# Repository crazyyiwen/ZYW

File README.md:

# ZYW

Dear everyone:

                  This part includes several projects I have done before
                  1 PMSM motor control prototype simulation in Matlab
                  
                  2 CAN PCB design connected to myRIO
                  
                  3 resolver signal processing for PMSM PCB design
                  
                  4 BLDC commercial project PCB design and control(C code)

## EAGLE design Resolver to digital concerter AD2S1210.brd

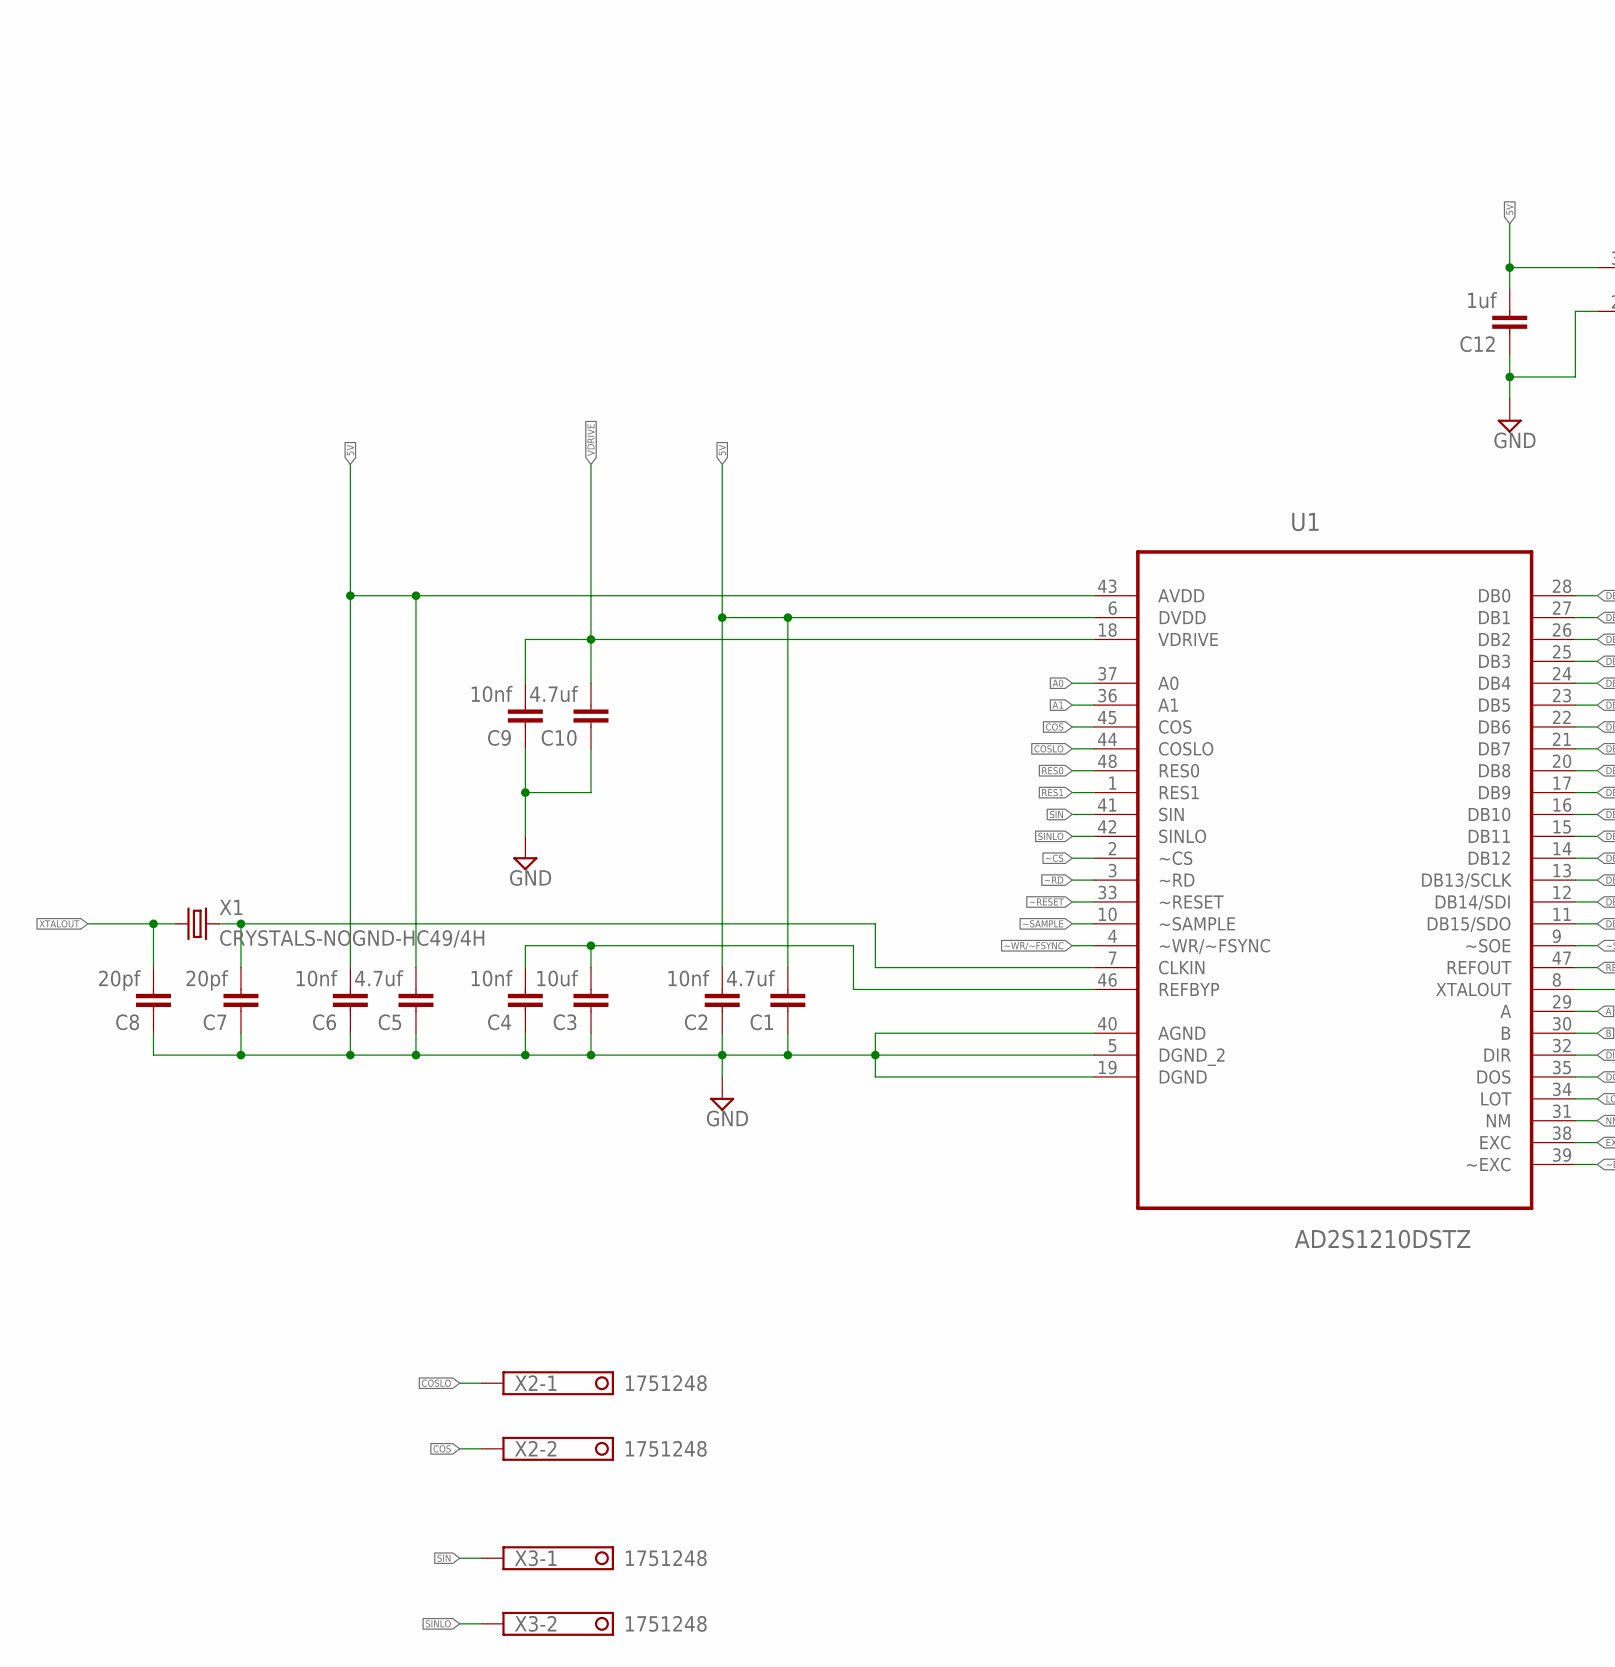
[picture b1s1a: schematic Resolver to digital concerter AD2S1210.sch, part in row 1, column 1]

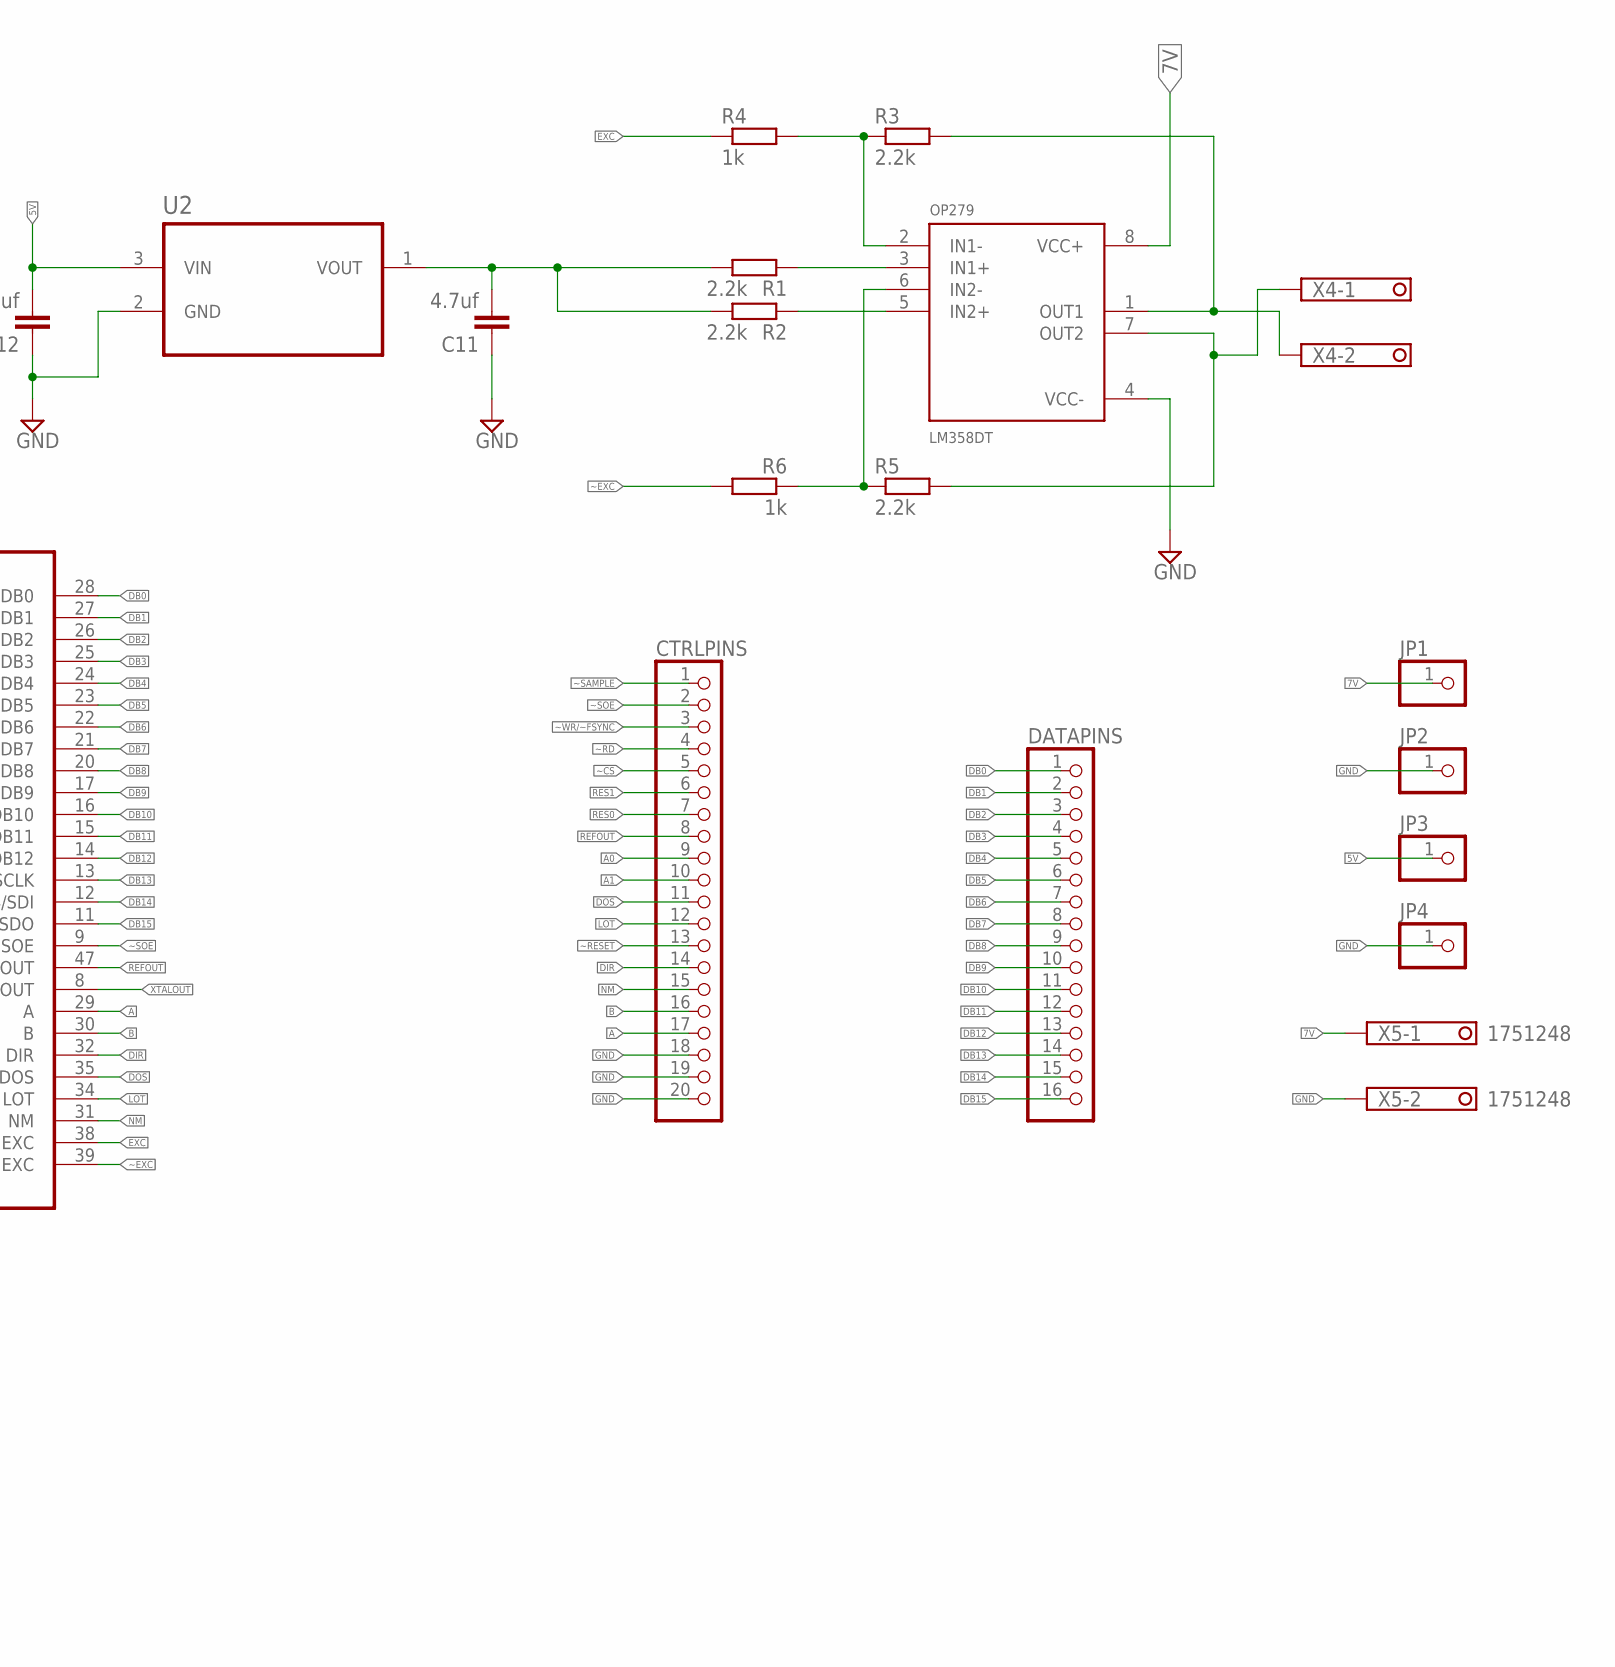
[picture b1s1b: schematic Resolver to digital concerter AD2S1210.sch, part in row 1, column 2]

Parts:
C1, C5, C10, C11: 4.7uf; C0805
C2, C4, C6, C9: 10nf; C0805
C3: 10uf; C0805
C7, C8: 20pf; C0805
C12: 1uf; C0805
CTRLPINS: PINHD-1X20; 1X20
DATAPINS: PINHD-1X16; 1X16
JP1, JP2, JP3, JP4: PINHD-1X1; 1X01
OP279: LM358DT; SOIC127P600X175-8N
R1, R2, R3, R5: 2.2k; R0805
R4, R6: 1k; R0805
U1: AD2S1210DSTZ; QFP50P900X900X160-48N
U2: AD1582BRTZ-REEL7; SOT95P237X112-3N
X1: CRYSTALS-NOGND-HC49/4H; HC49
X2, X3, X4, X5: 1751248

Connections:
5V: C1.2, C2.2, C5.2, C6.2, C12.2, JP3.1, U1.6 (DVDD), U1.43 (AVDD), U2.3 (VIN)
7V: JP1.1, OP279.8 (VCC+), X5.1
A: CTRLPINS.17, U1.29 (A)
A0: CTRLPINS.9, U1.37 (A0)
A1: CTRLPINS.10, U1.36 (A1)
B: CTRLPINS.16, U1.30 (B)
COS: U1.45 (COS), X2.2
COSLO: U1.44 (COSLO), X2.1
DB0: DATAPINS.1, U1.28 (DB0)
DB1: DATAPINS.2, U1.27 (DB1)
DB2: DATAPINS.3, U1.26 (DB2)
DB3: DATAPINS.4, U1.25 (DB3)
DB4: DATAPINS.5, U1.24 (DB4)
DB5: DATAPINS.6, U1.23 (DB5)
DB6: DATAPINS.7, U1.22 (DB6)
DB7: DATAPINS.8, U1.21 (DB7)
DB8: DATAPINS.9, U1.20 (DB8)
DB9: DATAPINS.10, U1.17 (DB9)
DB10: DATAPINS.11, U1.16 (DB10)
DB11: DATAPINS.12, U1.15 (DB11)
DB12: DATAPINS.13, U1.14 (DB12)
DB13: DATAPINS.14, U1.13 (DB13/SCLK)
DB14: DATAPINS.15, U1.12 (DB14/SDI)
DB15: DATAPINS.16, U1.11 (DB15/SDO)
DIR: CTRLPINS.14, U1.32 (DIR)
DOS: CTRLPINS.11, U1.35 (DOS)
EXC: R4.1, U1.38 (EXC)
GND: C1.1, C2.1, C3.1, C4.1, C5.1, C6.1, C7.1, C8.1, C9.1, C10.1, C11.1, C12.1, CTRLPINS.18, CTRLPINS.19, CTRLPINS.20, JP2.1, JP4.1, OP279.4 (VCC-), U1.5 (DGND_2), U1.19 (DGND), U1.40 (AGND), U2.2 (GND), X5.2
LOT: CTRLPINS.12, U1.34 (LOT)
unnamed: OP279.3 (IN1+), R1.1
unnamed: OP279.5 (IN2+), R2.1
unnamed: C11.2, R1.2, R2.2, U2.1 (VOUT)
unnamed: OP279.1 (OUT1), R3.2, X4.2
unnamed: OP279.2 (IN1-), R3.1, R4.2
unnamed: OP279.7 (OUT2), R5.2, X4.1
unnamed: OP279.6 (IN2-), R5.1, R6.1
unnamed: C3.2, C4.2, U1.46 (REFBYP)
unnamed: C7.2, U1.7 (CLKIN), X1.2
NM: CTRLPINS.15, U1.31 (NM)
REFOUT: CTRLPINS.8, U1.47 (REFOUT)
RES0: CTRLPINS.7, U1.48 (RES0)
RES1: CTRLPINS.6, U1.1 (RES1)
SIN: U1.41 (SIN), X3.1
SINLO: U1.42 (SINLO), X3.2
VDRIVE: C9.2, C10.2, U1.18 (VDRIVE)
XTALOUT: C8.2, U1.8 (XTALOUT), X1.1
~CS: CTRLPINS.5, U1.2 (~CS)
~EXC: R6.2, U1.39 (~EXC)
~RD: CTRLPINS.4, U1.3 (~RD)
~RESET: CTRLPINS.13, U1.33 (~RESET)
~SAMPLE: CTRLPINS.1, U1.10 (~SAMPLE)
~SOE: CTRLPINS.2, U1.9 (~SOE)
~WR/~FSYNC: CTRLPINS.3, U1.4 (~WR/~FSYNC)

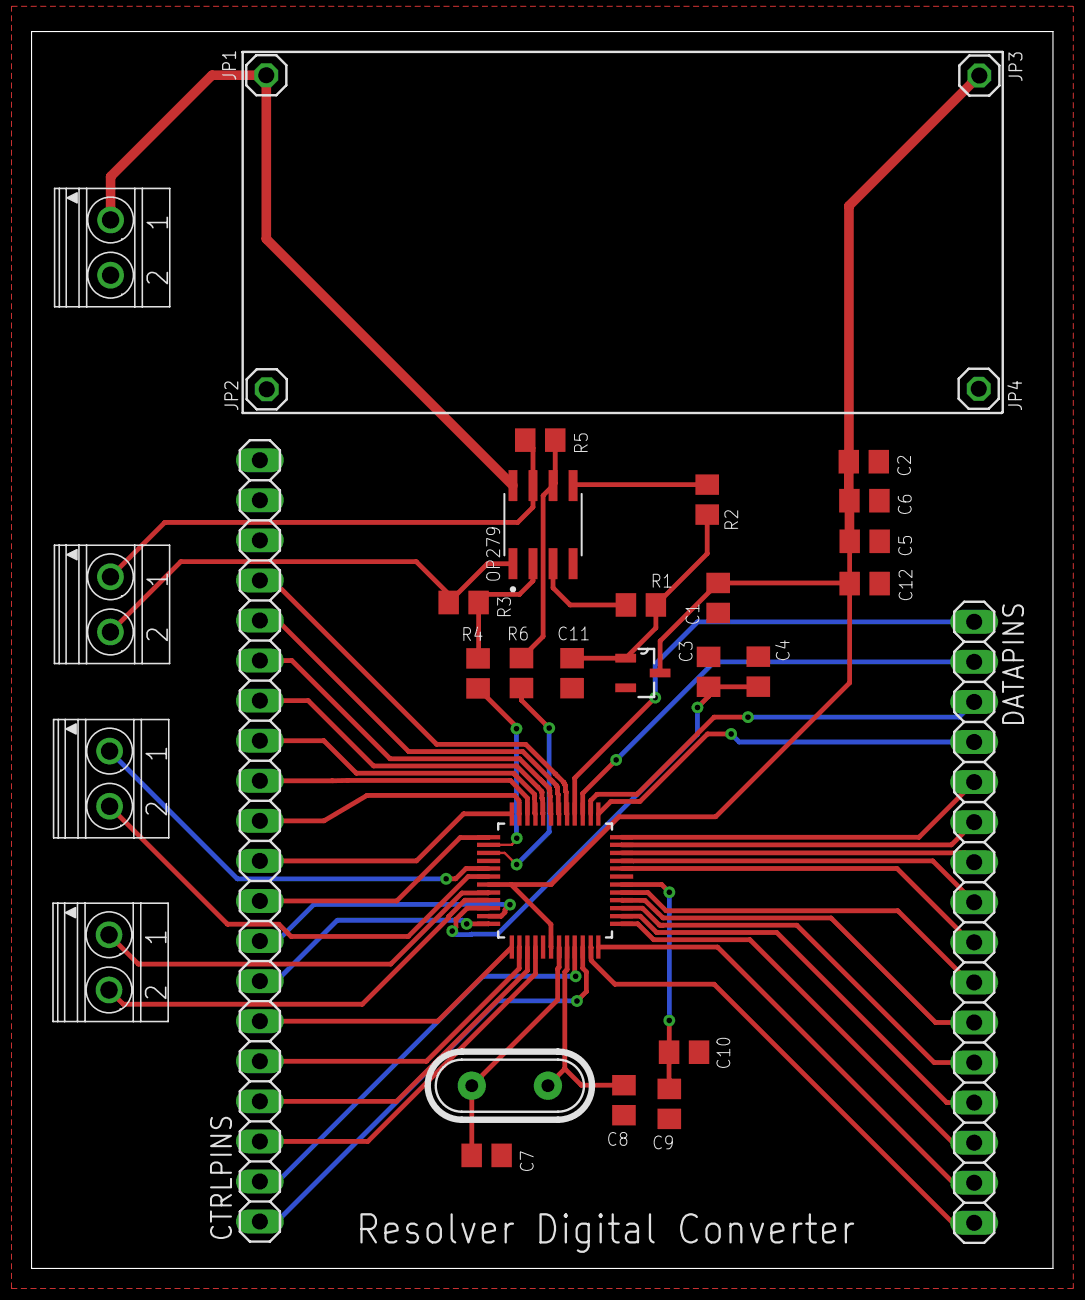
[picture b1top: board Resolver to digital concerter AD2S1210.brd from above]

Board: 2 copper layers, 64.8 x 78.4 mm, 32 parts (0 on the bottom side), 53 nets.

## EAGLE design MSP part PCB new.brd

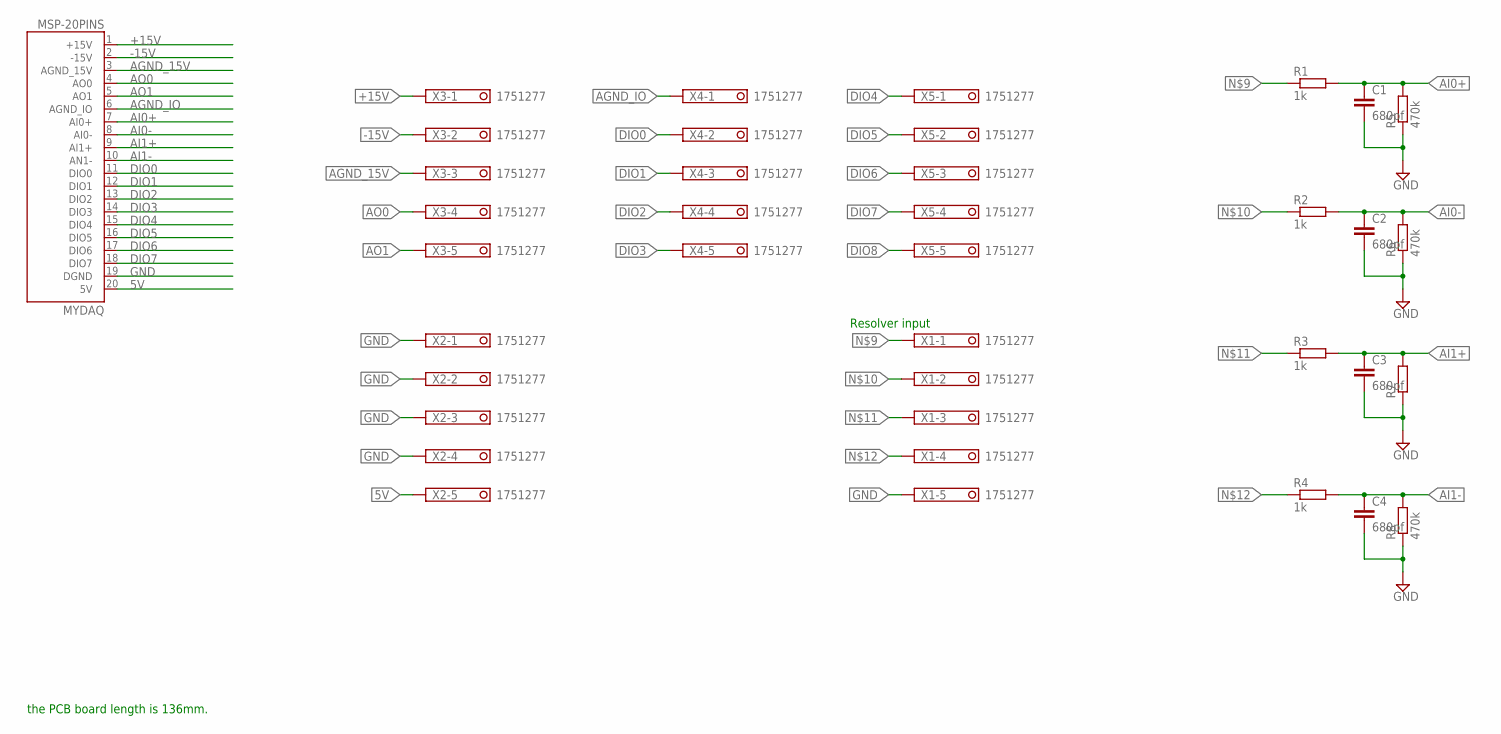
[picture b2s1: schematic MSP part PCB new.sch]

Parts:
C1, C2, C3, C4: 680pf; C050-024X044
MSP-20PINS: MYDAQ; 3.81MM_TERMINAL_BLOCK_FEMALE_LOCKING
R1, R2, R3, R4: 1k; 0204/7
R5, R6, R8: 470k; 0204/7
R7: R-EU_0204/7; 0204/7
X1, X2, X3, X4, X5: 1751277

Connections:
5V: MSP-20PINS.20 (5V), X2.5
+15V: MSP-20PINS.1 (+15V), X3.1
-15V: MSP-20PINS.2 (-15V), X3.2
AGND_15V: MSP-20PINS.3 (AGND_15V), X3.3
AGND_IO: MSP-20PINS.6 (AGND_IO), X4.1
AI0+: C1.1, MSP-20PINS.7 (AI0+), R1.2, R5.2
AI0-: C2.1, MSP-20PINS.8 (AI0-), R2.2, R6.2
AI1+: C3.1, MSP-20PINS.9 (AI1+), R3.2, R7.2
AI1-: C4.1, MSP-20PINS.10 (AN1-), R4.2, R8.2
AO0: MSP-20PINS.4 (AO0), X3.4
AO1: MSP-20PINS.5 (AO1), X3.5
DIO0: MSP-20PINS.11 (DIO0), X4.2
DIO1: MSP-20PINS.12 (DIO1), X4.3
DIO2: MSP-20PINS.13 (DIO2), X4.4
DIO3: MSP-20PINS.14 (DIO3), X4.5
DIO4: MSP-20PINS.15 (DIO4), X5.1
DIO5: MSP-20PINS.16 (DIO5), X5.2
DIO6: MSP-20PINS.17 (DIO6), X5.3
DIO7: MSP-20PINS.18 (DIO7), X5.4
DIO8: X5.5
GND: C1.2, C2.2, C3.2, C4.2, MSP-20PINS.19 (DGND), R5.1, R6.1, R7.1, R8.1, X1.5, X2.1, X2.2, X2.3, X2.4
unnamed: R1.1, X1.1
unnamed: R2.1, X1.2
unnamed: R3.1, X1.3
unnamed: R4.1, X1.4

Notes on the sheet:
Resolver input
the PCB board length is 136mm.

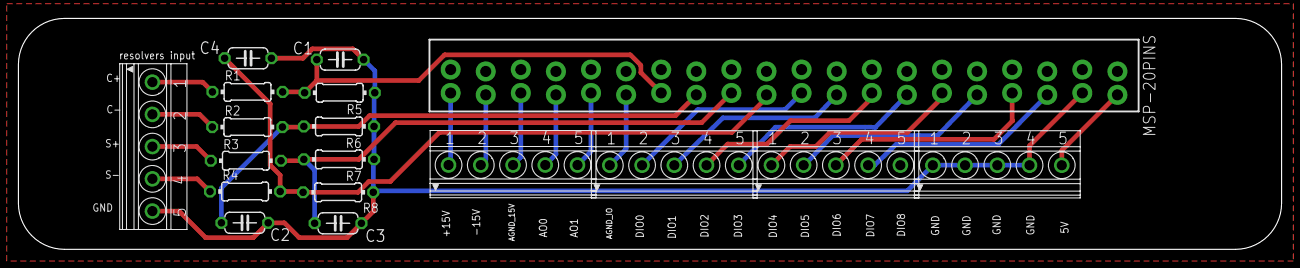
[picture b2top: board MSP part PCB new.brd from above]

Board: 2 copper layers, 137.1 x 25.1 mm, 18 parts (0 on the bottom side), 24 nets.

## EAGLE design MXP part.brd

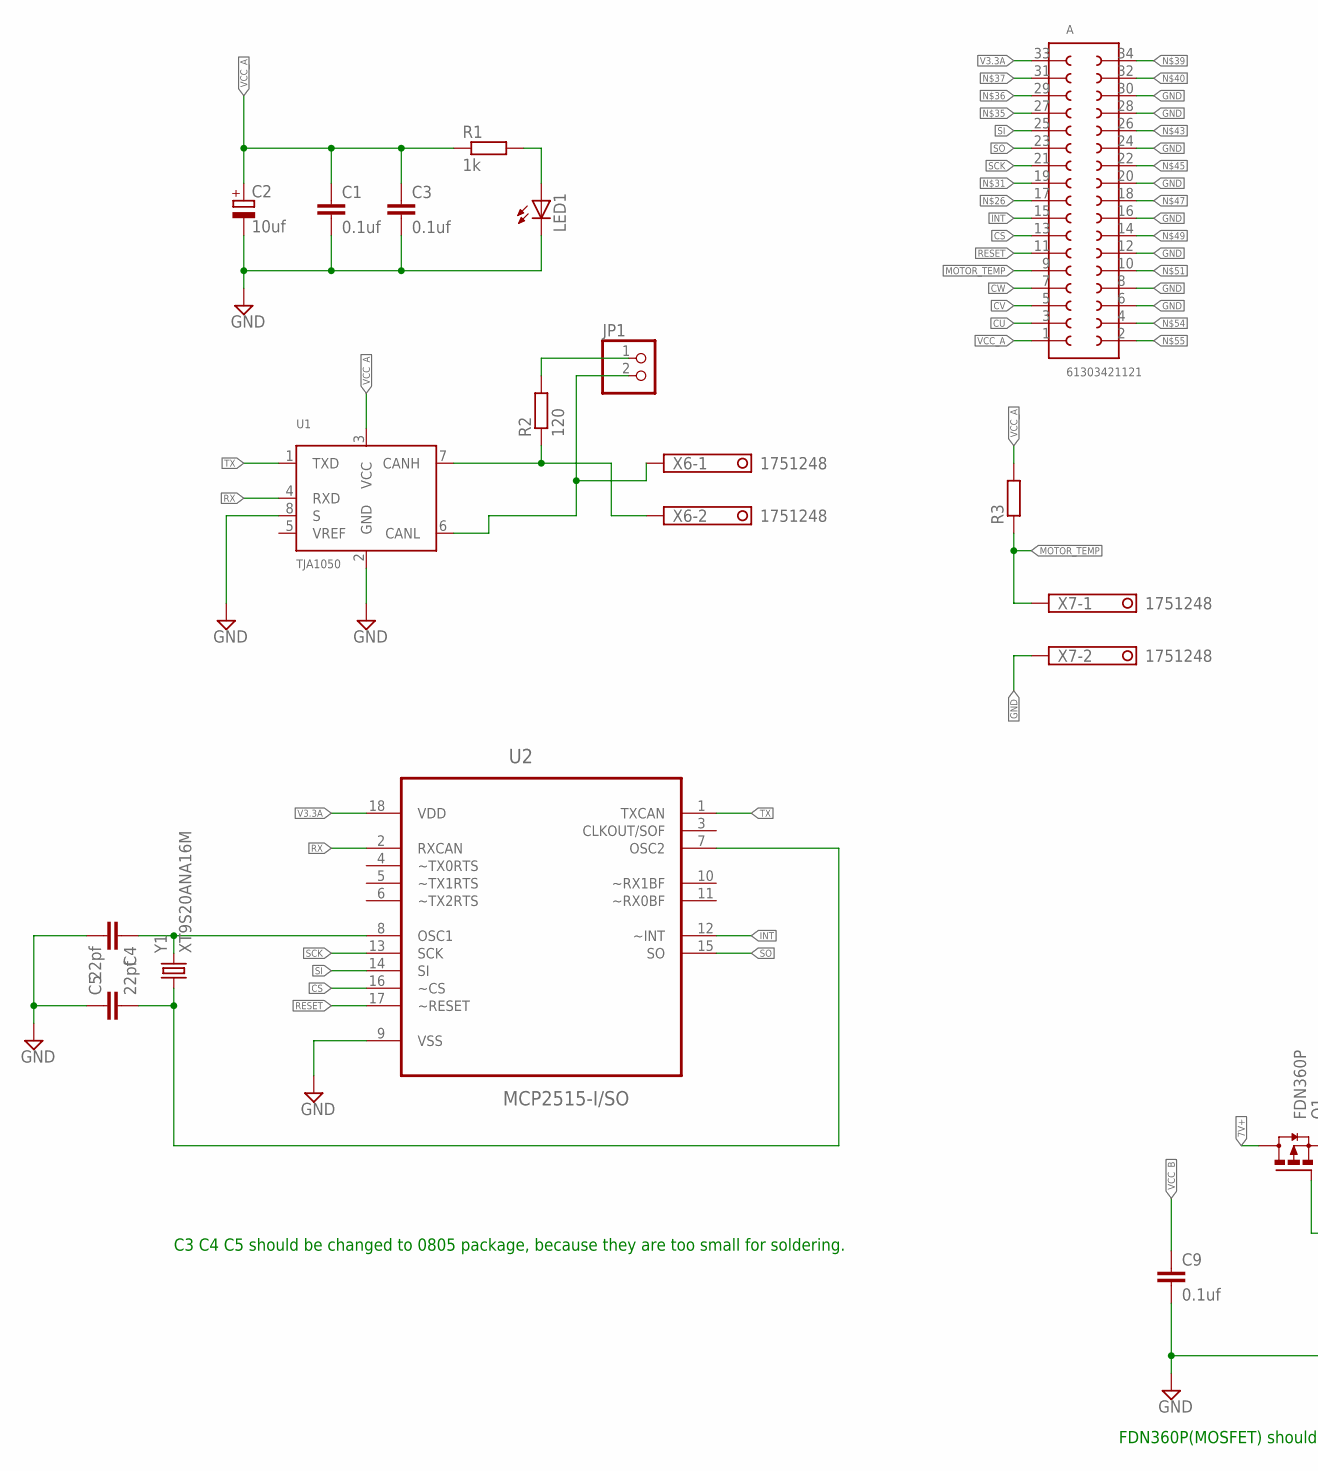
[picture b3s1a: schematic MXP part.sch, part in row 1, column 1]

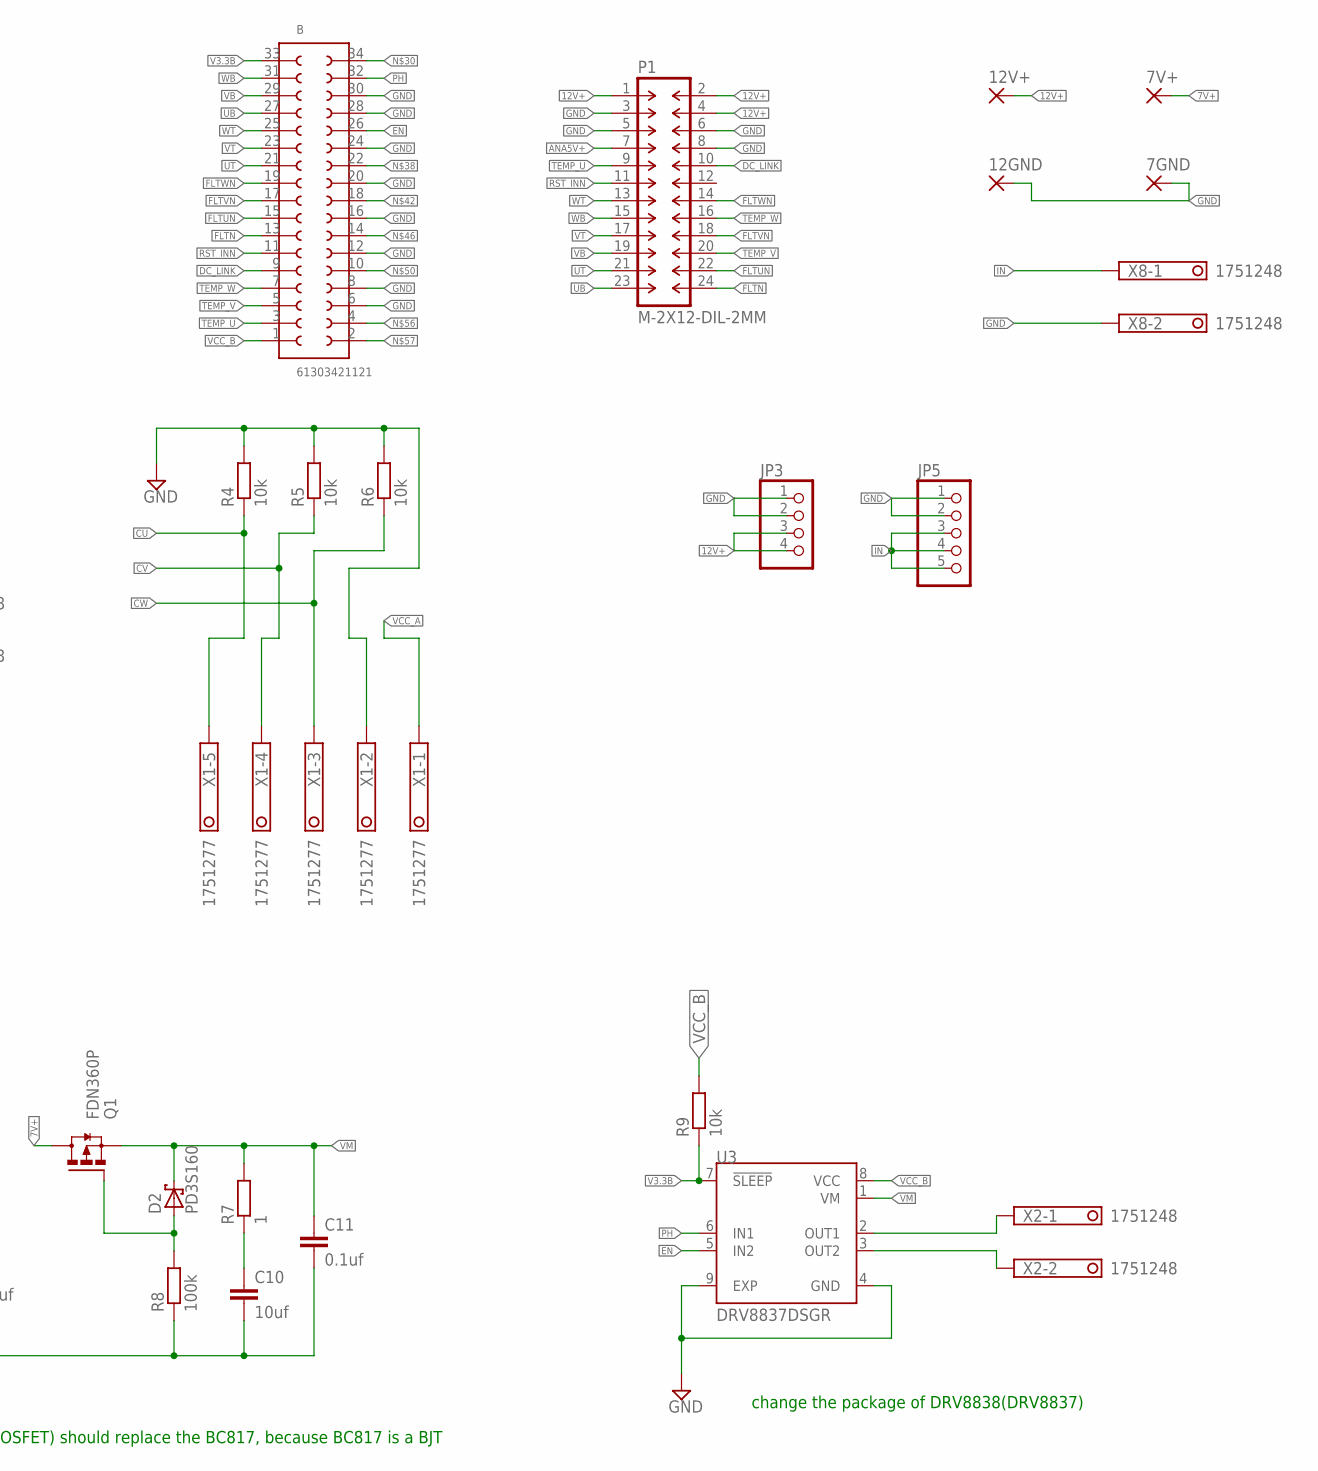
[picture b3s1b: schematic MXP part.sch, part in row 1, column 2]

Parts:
7GND, 7V+, 12GND, 12V+: 2,54/0,9
A: 61303421121
B: 61303421121
C1, C3: 0.1uf; C0402K
C2: 10uf; A/3216-18W
C4, C5: 22pf; C0402K
C9, C11: 0.1uf; C0603K
C10: 10uf; C0603K
D2: PD3S160; POWERDI323
JP1: PINHD-1X2; 1X02
JP3: PINHD-1X4; 1X04
JP5: PINHD-1X5; 1X05
LED1: LEDCHIP-LED0805; CHIP-LED0805
P1: M-2X12-DIL-2MM; DIL-2MM-2X12
Q1: FDN360P; SUPER-SOT3
R1: 1k; R0603
R2: 120; R0603
R3: R-EU_0204/7; 0204/7
R4, R5, R6: 10k; 0204/7
R7: 1; R0603
R8: 100k; R0603
R9: 10k; R0603
U1: TJA1050; SOT96-1
U2: MCP2515-I/SO; SOIC127P1034X264-18N
U3: DRV8837DSGR; SON50P200X200X80-9N
X1: 1751277
X2, X6, X7, X8: 1751248
Y1: XT9S20ANA16M; XTAL_XT9S20ANA16M

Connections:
7V+: 7V+.1, Q1.3 (D)
12V+: 12V+.1, JP3.3, JP3.4, P1.1, P1.2, P1.4
ANA5V+: P1.7
CS: A.13, U2.16 (~CS)
CU: A.3, R4.1, X1.5
CV: A.5, R5.1, X1.4
CW: A.7, R6.1, X1.3
DC_LINK: B.9, P1.10
EN: B.26, U3.5 (IN2)
FLTN: B.13, P1.24
FLTUN: B.15, P1.22
FLTVN: B.17, P1.18
FLTWN: B.19, P1.14
GND: 7GND.1, 12GND.1, A.6, A.8, A.12, A.16, A.20, A.24, A.28, A.30, B.6, B.8, B.12, B.16, B.20, B.24, B.28, B.30, C1.2, C2.-, C3.2, C4.2, C5.1, C9.2, C10.2, C11.2, JP3.1, JP3.2, JP5.1, JP5.2, LED1.C, P1.3, P1.5, P1.6, P1.8, R4.2, R5.2, R6.2, R8.1, U1.2 (GND), U1.8 (S), U2.9 (VSS), U3.4 (GND), U3.9 (EXP), X1.2, X7.2, X8.2
IN: JP5.3, JP5.4, JP5.5, X8.1
INT: A.15, U2.12 (~INT)
MOTOR_TEMP: A.9, R3.1, X7.1
unnamed: C4.1, U2.8 (OSC1), Y1.2
unnamed: JP1.1, R2.2
unnamed: C5.2, U2.7 (OSC2), Y1.1
unnamed: LED1.A, R1.2
unnamed: R2.1, U1.7 (CANH), X6.2
unnamed: JP1.2, U1.6 (CANL), X6.1
unnamed: U3.2 (OUT1), X2.1
unnamed: U3.3 (OUT2), X2.2
unnamed: D2.A, Q1.1 (G), R8.2
unnamed: C10.1, R7.1
PH: B.32, U3.6 (IN1)
RESET: A.11, U2.17 (~RESET)
RST_INN: B.11, P1.11
RX: U1.4 (RXD), U2.2 (RXCAN)
SCK: A.21, U2.13 (SCK)
SI: A.25, U2.14 (SI)
SO: A.23, U2.15 (SO)
TEMP_U: B.3, P1.9
TEMP_V: B.5, P1.20
TEMP_W: B.7, P1.16
TX: U1.1 (TXD), U2.1 (TXCAN)
UB: B.27, P1.23
UT: B.21, P1.21
V3.3A: A.33, U2.18 (VDD)
V3.3B: B.33, R9.1, U3.7 (!SLEEP)
VB: B.29, P1.19
VCC_A: A.1, C1.1, C2.+, C3.1, R1.1, R3.2, U1.3 (VCC), X1.1
VCC_B: B.1, C9.1, R9.2, U3.8 (VCC)
VM: C11.1, D2.C, Q1.2 (S), R7.2, U3.1 (VM)
VT: B.23, P1.17
WB: B.31, P1.15
WT: B.25, P1.13

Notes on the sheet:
C3 C4 C5 should be changed to 0805 package, because they are too small for soldering.
change the package of DRV8838(DRV8837)
FDN360P(MOSFET) should replace the BC817, because BC817 is a BJT

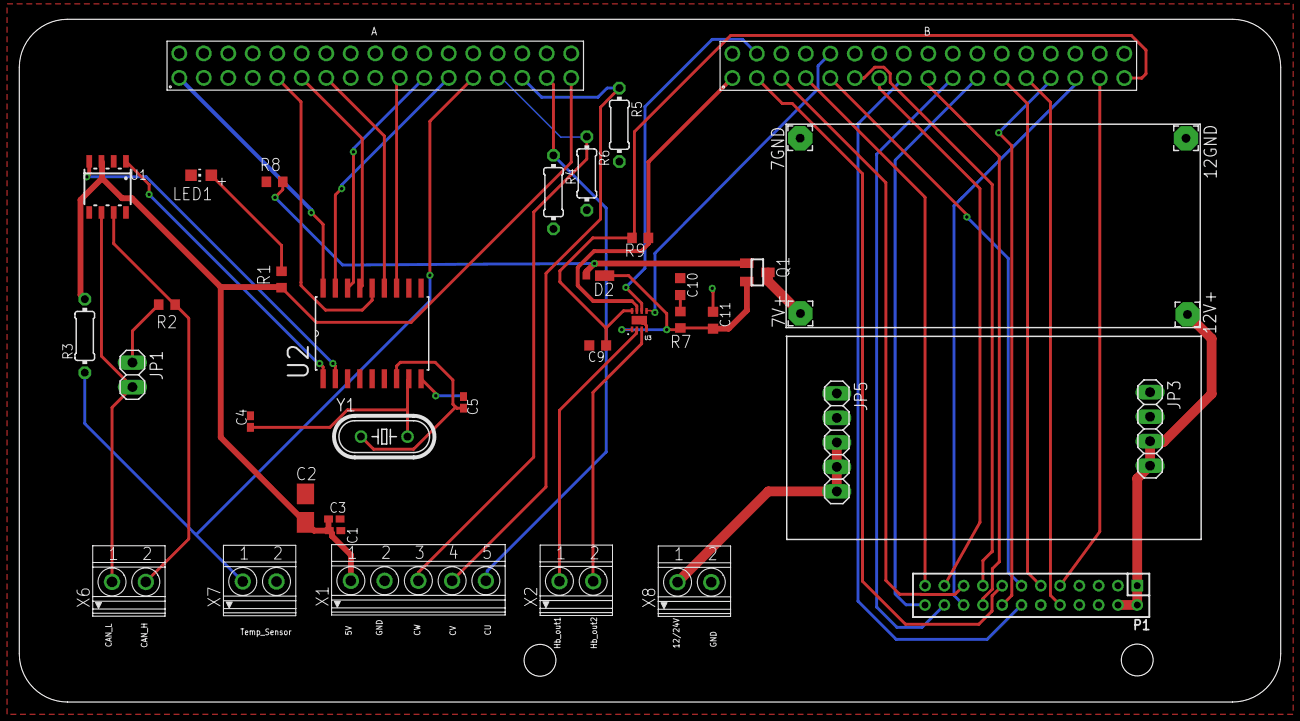
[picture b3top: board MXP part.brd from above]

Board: 2 copper layers, 130.8 x 70.8 mm, 39 parts (0 on the bottom side), 48 nets.

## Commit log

2016-11-07 Create JavaTest
2019-02-25 Add files via upload
    MXP part CAN BUS and DC-DC and H bridge
2019-02-25 Add files via upload
    MSP Part
2019-02-25 Add files via upload
    Matlab 3-phase PMSM

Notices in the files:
parts and their libraries:
con-headers-jp: Copyright (C) 2008, Bob Starr
NXP_60_26022015: This library may be distributed and adapted freely for any purpose, as long as NXP is credited and any new creation is licensed under the same terms.
